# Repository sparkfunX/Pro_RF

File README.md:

SparkFun ProRF with RFM69/RFM95 LoRa
========================================

[*SparkX ProRF (SPX-14785)*](https://www.sparkfun.com/products/14785)

The Pro RF is the mind meld of a Pro Micro and a long-range RFM95W LoRa®-enabled radio. What you get is a very compact, easy to use Arduino with excellent point to point data transmission in the 915MHz ISM band. The Pro RF comes with a LiPo connector, a on-board LiPo charger, and a slide switch for On/Off. The board programs over a reinforced microB connector with a sleek reset button that fits nicely on the side of the board. We've even added our popular [Qwiic connector](https://www.sparkfun.com/qwiic) to the edge of the board making it incredibly fast to add sensors and actuators.

Thanks to the [Arduino LoRa library](https://github.com/sandeepmistry/arduino-LoRa), the RFM95W radio is an easy to use packet radio. But it doesn't stop at point-to-point packet radio because closing a few jumpers will give the Pro RF access to the DIO pins on the RFM95W which are necessary to operate in LoRaWAN mode, so you can use the Pro RF as a LoRaWAN node in a distributed sensor network such as [The Things Network](https://www.thethingsnetwork.org/).

The Pro RF also includes a power switch and 2-pin JST connector for powering from a lithium battery. With the power switch in the off position, the Pro RF will even charge the attached battery! 

And stop running out of ground pins! Every pin on the Pro RF is accompanied with a ground connection making buttons and LEDs super easy to connect. And in case your building something to be embedded into clothing or other physically harsh environment the antenna includes a stress relief hole to make sure your wire antenna survives.

Although a short (3 inch) wire antenna is sufficient for short distances (up to 1 mile line-of-sight), LoRa® is theoretically capable of covering extremely long distances (several miles) using the proper antenna. We've included the sketches we used for [range testing](https://cdn.sparkfun.com/assets/7/d/b/4/f/ProRF_RFM95.zip).

Checkout the [Pro Micro hookup guide](https://learn.sparkfun.com/tutorials/pro-micro--fio-v3-hookup-guide) as a general starting point for the Pro RF.

SparkFun labored with love to create this code. Feel like supporting open source hardware? 
Buy a [breakout board](https://www.sparkfun.com/products/14785) from SparkFun!

Repository Contents
-------------------

* **/Examples** - Example sketches showing how to setup the radio for maximuim range
* **/Hardware** - Eagle design files (.brd, .sch)

License Information
-------------------

This product is _**open source**_! 

If you have any questions or concerns on licensing, please contact techsupport@sparkfun.com.

Please use, reuse, and modify these files as you see fit. Please maintain attribution to SparkFun Electronics and release any derivative under the same license.

Distributed as-is; no warranty is given.

- Your friends at SparkFun.

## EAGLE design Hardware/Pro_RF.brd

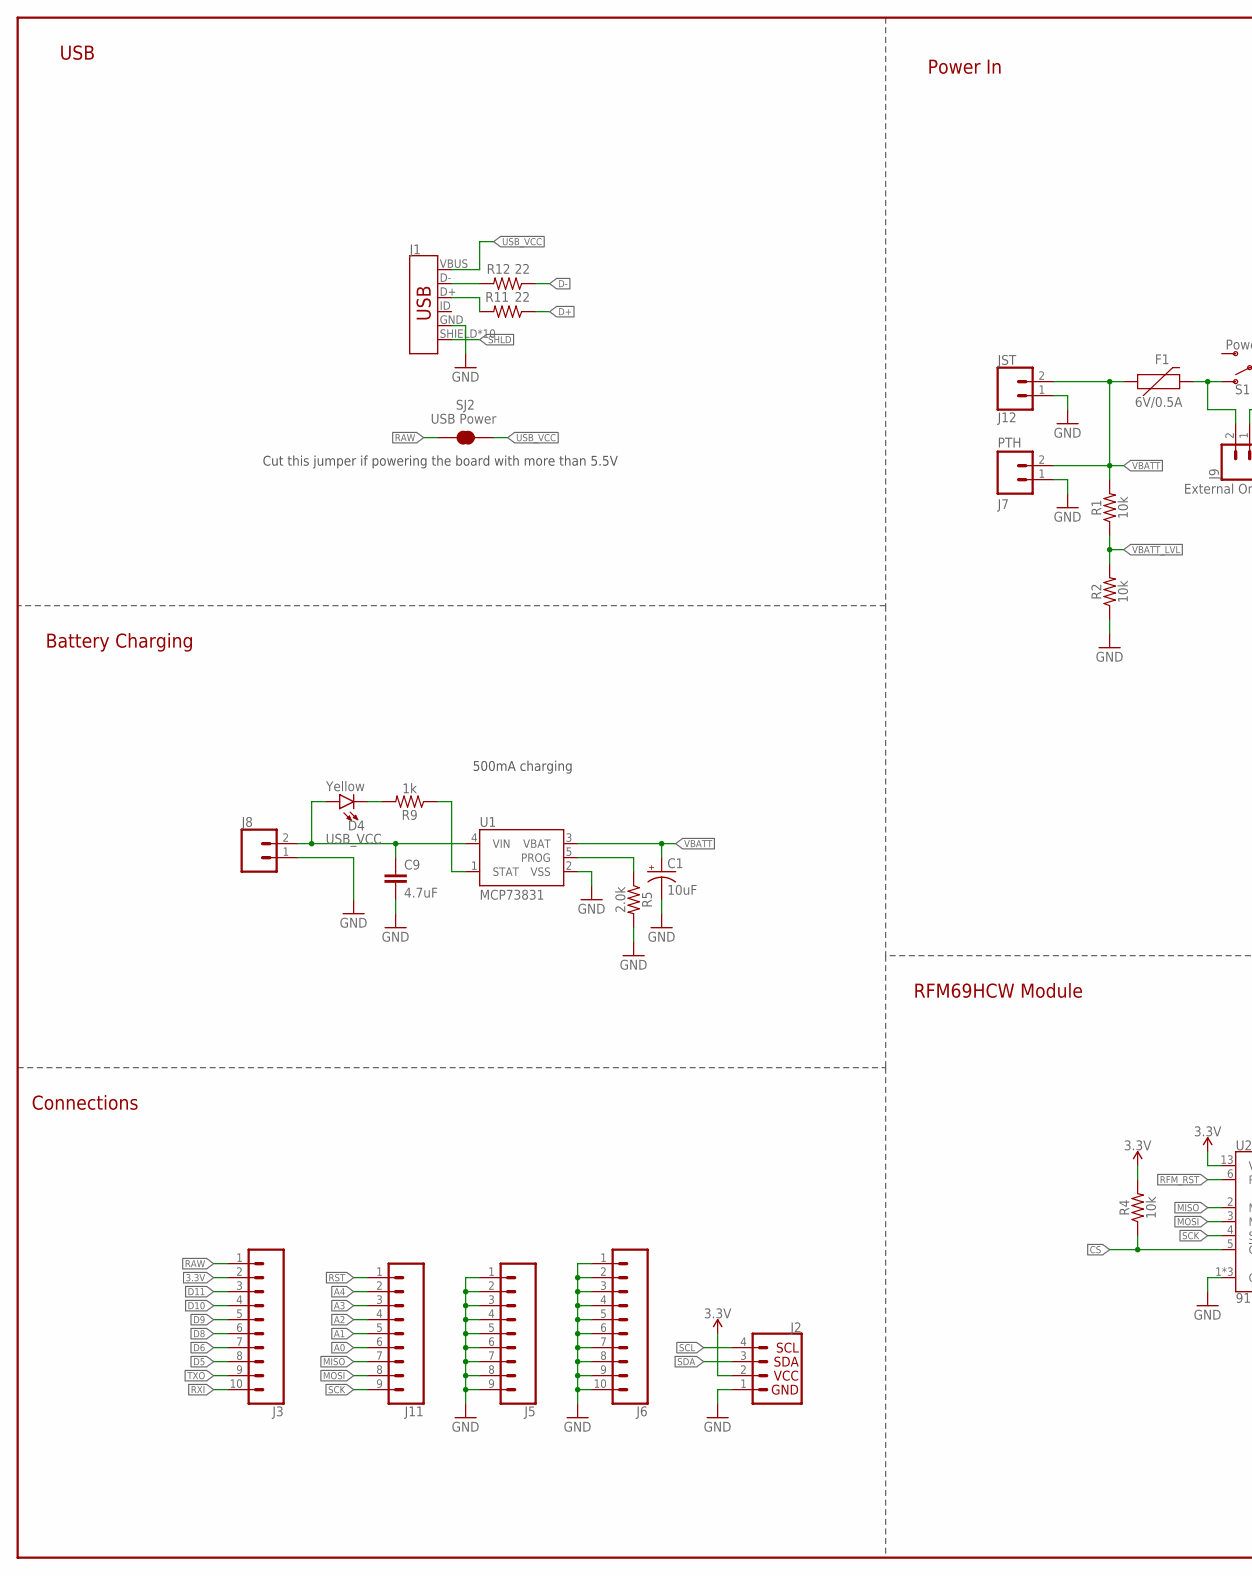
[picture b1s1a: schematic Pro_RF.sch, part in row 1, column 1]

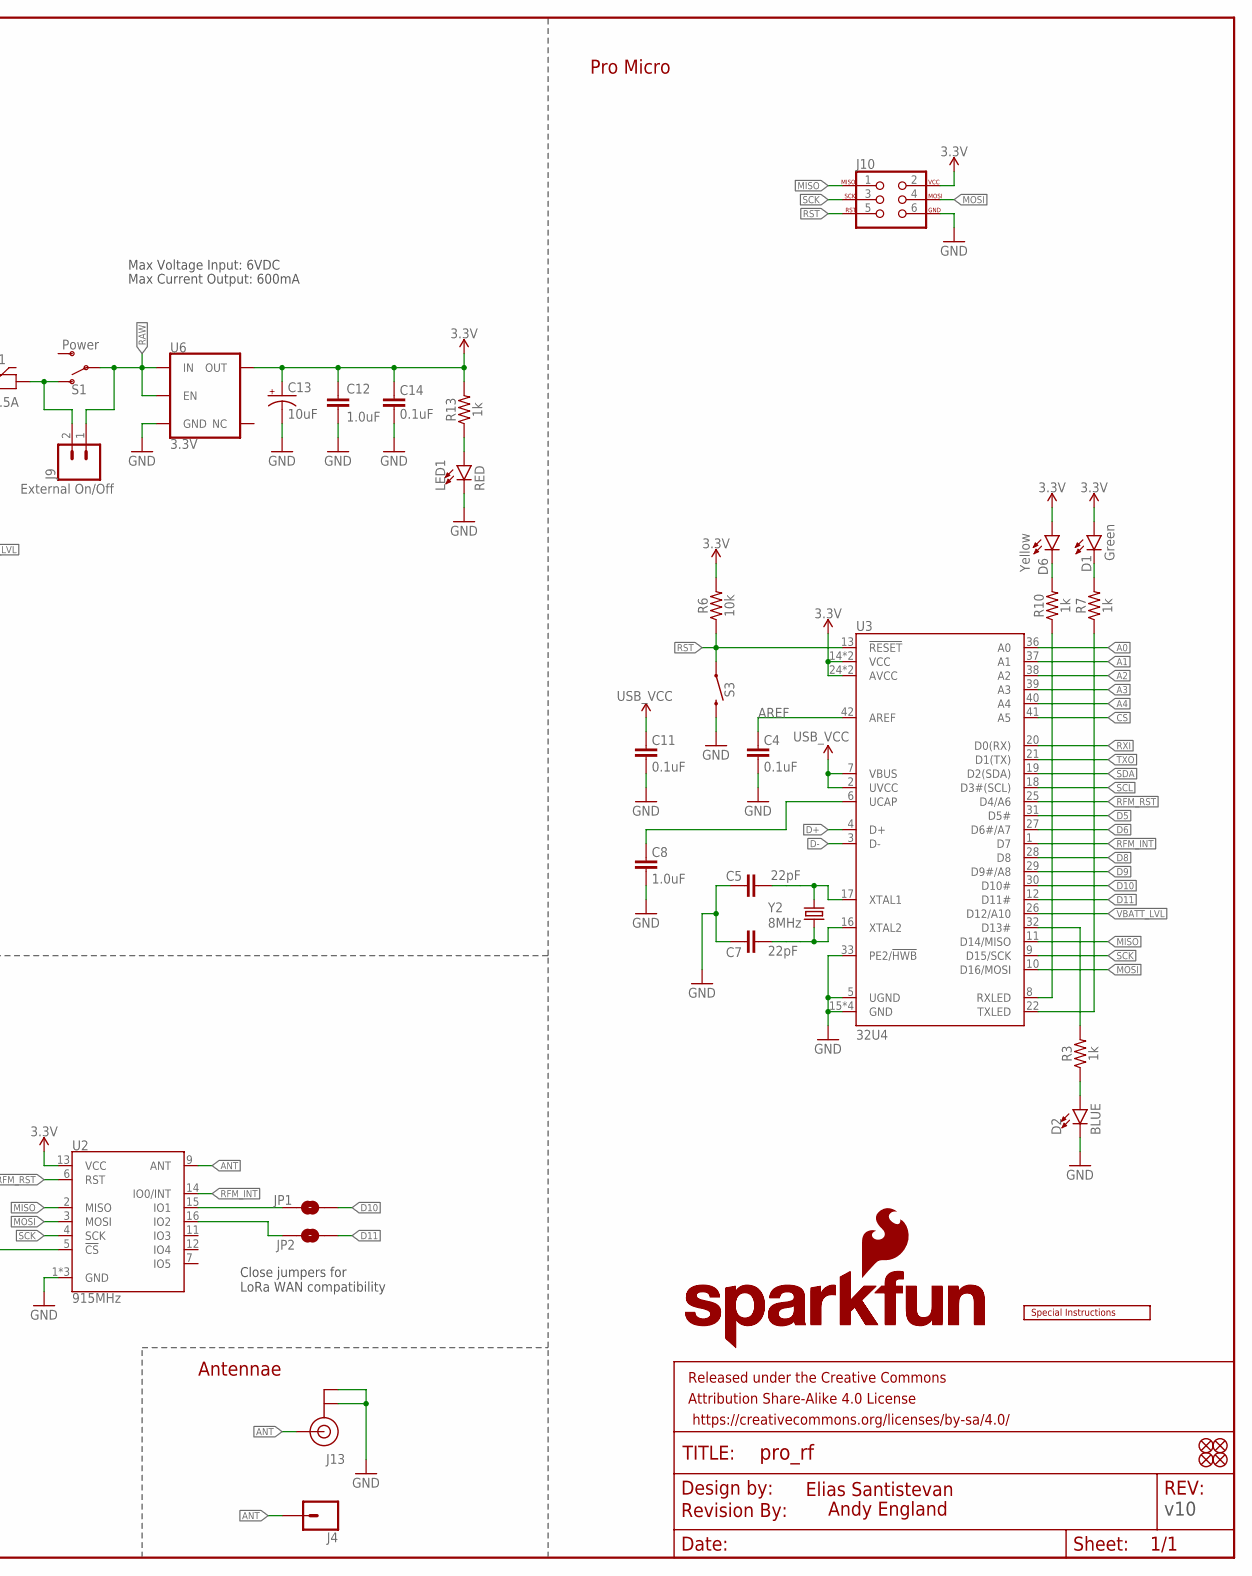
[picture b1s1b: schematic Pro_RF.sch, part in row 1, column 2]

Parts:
C1, C13: 10uF; EIA3216
C4, C11, C14: 0.1uF; 0603
C5, C7: 22pF; 0603
C8, C12: 1.0uF; 0603
C9: 4.7uF; 0603
D1: Green; LED-0603
D2: BLUE; LED-0603
D4, D6: Yellow; LED-0603
F1: 6V/0.5A; 1206
FD1, FD2, FD3, FD4: FIDUCIAL1X2; FIDUCIAL-1X2
FRAME2: FRAME-LEDGER; CREATIVE_COMMONS
J1: USB_MICRO-B_HALF_PTH_MILL; USB-MICROB-PTH-MILL
J2: QWIIC_CONNECTORJS-1MM; 1X04_1MM_RA
J3, J6: CONN_10NO_SILK_PTH_FEMALE; 1X10_NO_SILK
J4: CONN_01PTH_NO_SILK_YES_STOP; 1X01_NO_SILK
J5, J11: CONN_09NO_SILK; 1X09_NO_SILK
J7: PTH; 1X02_NO_SILK
J8: CONN_021X02_NO_SILK; 1X02_NO_SILK
J9: External On/Off; 1X02_NO_SILK
J10: AVR_SPI_PROG_3X2TESTPOINTS; 2X3_TEST_POINTS
J12: JST; JST-2-SMD
J13: U.FL
JP1, JP2: JUMPER-SMT_2_NO_SILK; SMT-JUMPER_2_NO_SILK
LED1: RED; LED-0603
LOGO1: REVISION
LOGO2: SFE_LOGO_NAME.1_INCH; SFE_LOGO_NAME_.1
LOGO3: SFE_LOGO_NAME_FLAME.1_INCH; SFE_LOGO_NAME_FLAME_.1
R1, R2, R4, R6: 10k; 0603
R3, R7, R9, R10, R13: 1k; 0603
R5: 2.0k; 0603
R11, R12: 22; 0603
S1: Power; SWITCH_SPST_SMD_A
S3: MOMENTARY-SWITCH-SPST-SMD-RIGHT-ANGLE; TACTILE_SWITCH_SMD_RIGHT_ANGLE
SJ2: USB Power; SMT-JUMPER_2_NC_TRACE_SILK
U1: MCP73831; SOT23-5
U2: 915MHz; RFM69HCW-XXXS2
U3: 32U4; QFN-44-NOPAD
U6: 3.3V; SOT23-5
U$26: SPECIAL_INSTRUCTIONS-ORDERING; ORDERING_INSTRUCTIONS
Y2: 8MHz; CRYSTAL-SMD-5X3.2-4PAD

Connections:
3.3V: C12.1, C13.+, C14.2, D1.A, D6.A, J2.2, J3.2, J10.2, R4.2, R6.2, R13.2, U2.13 (VCC), U3.14 (VCC), U3.24 (AVCC), U3.34 (VCC), U3.44 (AVCC), U6.5 (OUT)
!CS: R4.1, U2.5 (!CS), U3.41 (A5)
!RST: J10.5, J11.1, R6.1, S3.1, U3.13 (!RESET)
A0: J11.6, U3.36 (A0)
A1: J11.5, U3.37 (A1)
A2: J11.4, U3.38 (A2)
A3: J11.3, U3.39 (A3)
A4: J11.2, U3.40 (A4)
ANT: J4.1, J13.FEED (SIGNAL), U2.9 (ANT)
AREF: C4.2, U3.42 (AREF)
CHARGE_STAT: R9.1, U1.1 (STAT)
D5: J3.8, U3.31 (D5#)
D6: J3.7, U3.27 (D6#/A7)
D8: J3.6, U3.28 (D8)
D9: J3.5, U3.29 (D9#/A8)
D10: J3.4, JP1.2, U3.30 (D10#)
D11: J3.3, JP2.2, U3.12 (D11#)
D+: R11.1, U3.4 (D+)
D-: R12.1, U3.3 (D-)
GND: C1.-, C4.1, C5.2, C7.2, C8.1, C9.2, C11.1, C12.2, C13.-, C14.1, D2.C, J1.GND, J2.1, J5.1, J5.2, J5.3, J5.4, J5.5, J5.6, J5.7, J5.8, J5.9, J6.1, J6.2, J6.3, J6.4, J6.5, J6.6, J6.7, J6.8, J6.9, J6.10, J7.1, J8.1, J10.6, J12.1 (2), J13.1 (GND), J13.2 (GND), LED1.C, R2.1, R5.2, S3.2, U1.2 (VSS), U2.1 (GND), U2.8 (GND), U2.10 (GND), U3.5 (UGND), U3.15 (GND), U3.23 (GND), U3.33 (PE2/!HWB), U3.35 (GND), U3.43 (GND), U6.2 (GND)
MISO: J10.1, J11.7, U2.2 (MISO), U3.11 (D14/MISO)
MOSI: J10.4, J11.8, U2.3 (MOSI), U3.10 (D16/MOSI)
unnamed: D6.C, R10.2
unnamed: D1.C, R7.2
unnamed: D2.A, R3.1
unnamed: C5.1, U3.17 (XTAL1), Y2.3 (2)
unnamed: J1.D+, R11.2
unnamed: C7.1, U3.16 (XTAL2), Y2.1
unnamed: D4.C, R9.2
unnamed: F1.2, J9.2, S1.1 (O)
unnamed: R5.1, U1.5 (PROG)
unnamed: J1.D-, R12.2
unnamed: LED1.A, R13.1
RAW: J3.1, J9.1, S1.2, SJ2.1, U6.1 (IN), U6.3 (EN)
RFM_INT: U2.14 (IO0/INT), U3.1 (D7)
RFM_IO1: JP1.1, U2.15 (IO1)
RFM_IO2: JP2.1, U2.16 (IO2)
RFM_RST: U2.6 (RST), U3.25 (D4/A6)
RXI: J3.10, U3.20 (D0(RX))
RXLED: R10.1, U3.8 (RXLED)
SCK: J10.3, J11.9, U2.4 (SCK), U3.9 (D15/SCK)
SCL: J2.4, U3.18 (D3#(SCL))
SDA: J2.3, U3.19 (D2(SDA))
SHLD: J1.SHIELD, J1.SHIELD2 (SHIELD), J1.SHIELD3 (SHIELD), J1.SHIELD4 (SHIELD), J1.SHIELD5 (SHIELD), J1.SHIELD6 (SHIELD), J1.SHIELD7 (SHIELD), J1.SHIELD8 (SHIELD), J1.SHIELD9 (SHIELD), J1.SHIELD10 (SHIELD)
STAT: R3.2, U3.32 (D13#)
TXLED: R7.1, U3.22 (TXLED)
TXO: J3.9, U3.21 (D1(TX))
UCAP: C8.2, U3.6 (UCAP)
USB_VCC: C9.1, C11.2, D4.A, J1.VBUS, J8.2, SJ2.2, U1.4 (VIN), U3.2 (UVCC), U3.7 (VBUS)
VBATT: C1.+, F1.1, J7.2, J12.2 (1), R1.2, U1.3 (VBAT)
VBATT_LVL: R1.1, R2.2, U3.26 (D12/A10)

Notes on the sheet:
Max Voltage Input: 6VDC
Max Current Output: 600mA
Cut this jumper if powering the board with more than 5.5V
500mA charging
Close jumpers for LoRa WAN compatibility
Battery Charging
Power In
Pro Micro
RFM69HCW Module
v10
Andy England
Connections
Elias Santistevan
USB
Antennae

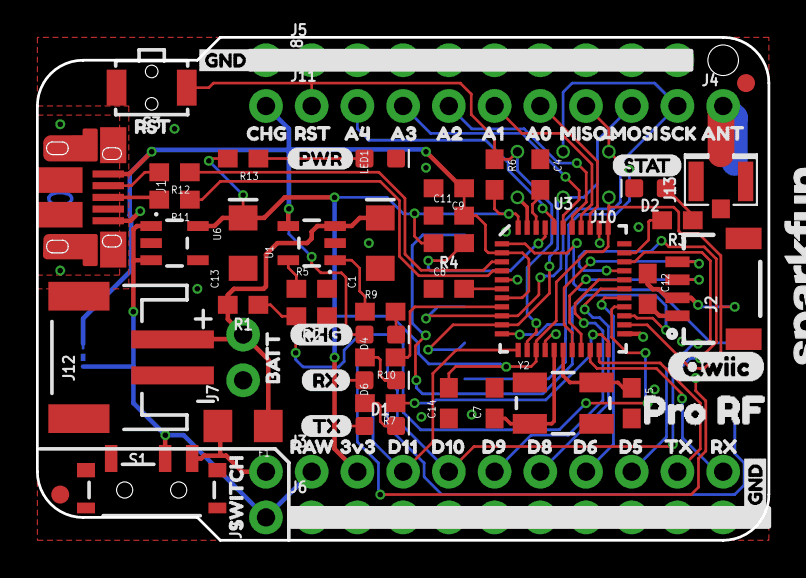
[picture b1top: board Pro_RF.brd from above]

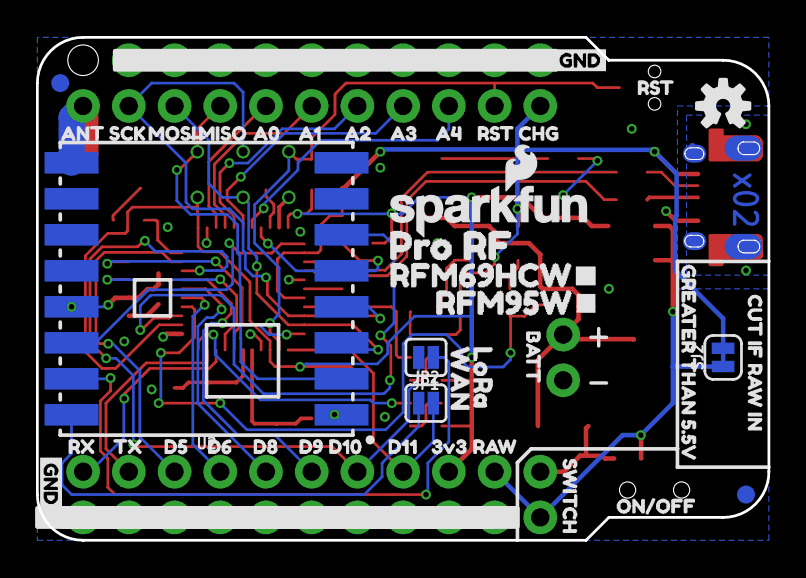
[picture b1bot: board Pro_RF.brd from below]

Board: 2 copper layers, 40.6 x 27.9 mm, 128 parts (42 on the bottom side), 51 nets.

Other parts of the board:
U$1, U$31: PRO_RF0
U$3, U$42: A43
U$4, U$43: A34
U$5, U$44: A25
U$6, U$45: A16
U$7, U$46: A07
U$8, U$47: MISO8
U$9, U$48: MOSI9
U$10, U$49: SCK10
U$11, U$50: ANT11
U$12, U$17, U$38, U$62: GND0
U$13, U$28, U$36, U$41: RST2
U$14, U$40, U$65: CHG1
U$15, U$16: D90
U$18, U$58: D615
U$19, U$73: RX2
U$20, U$56: D817
U$21, U$68: D100
U$22, U$54: D1119
U$23, U$53: 3V320
U$24, U$52: RAW21
U$25: LORA0
U$27, U$37: SWITCH23
U$29, U$32: BATT25
U$33: CUT_IF_RAW_IN0
U$34: GREATER_THAN_5#5V1
U$35: WAN1
U$39: ON#OFF0
U$51: OSHW-LOGO-S
U$55, U$74: D514
U$57, U$69: TX3
U$59: RFM69HCW#1
U$60: RFM95W#0
U$63: PWR-()-03
U$66: QWIIC-()-04
U$70: TX6
U$71: STAT5
U$72: RX7

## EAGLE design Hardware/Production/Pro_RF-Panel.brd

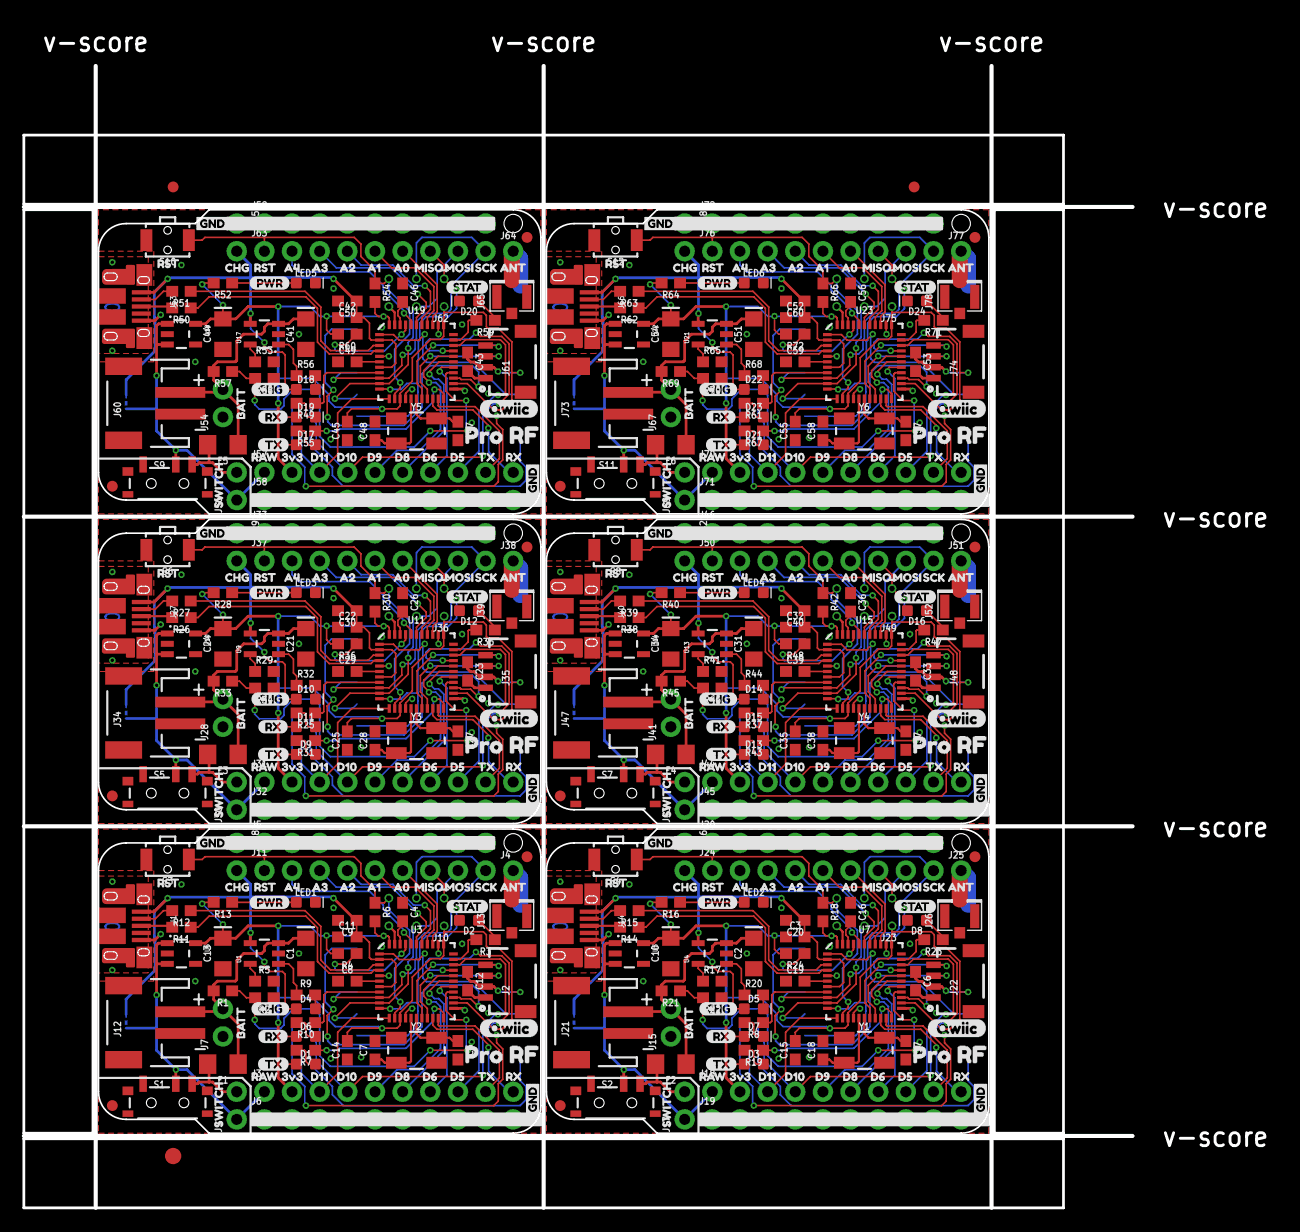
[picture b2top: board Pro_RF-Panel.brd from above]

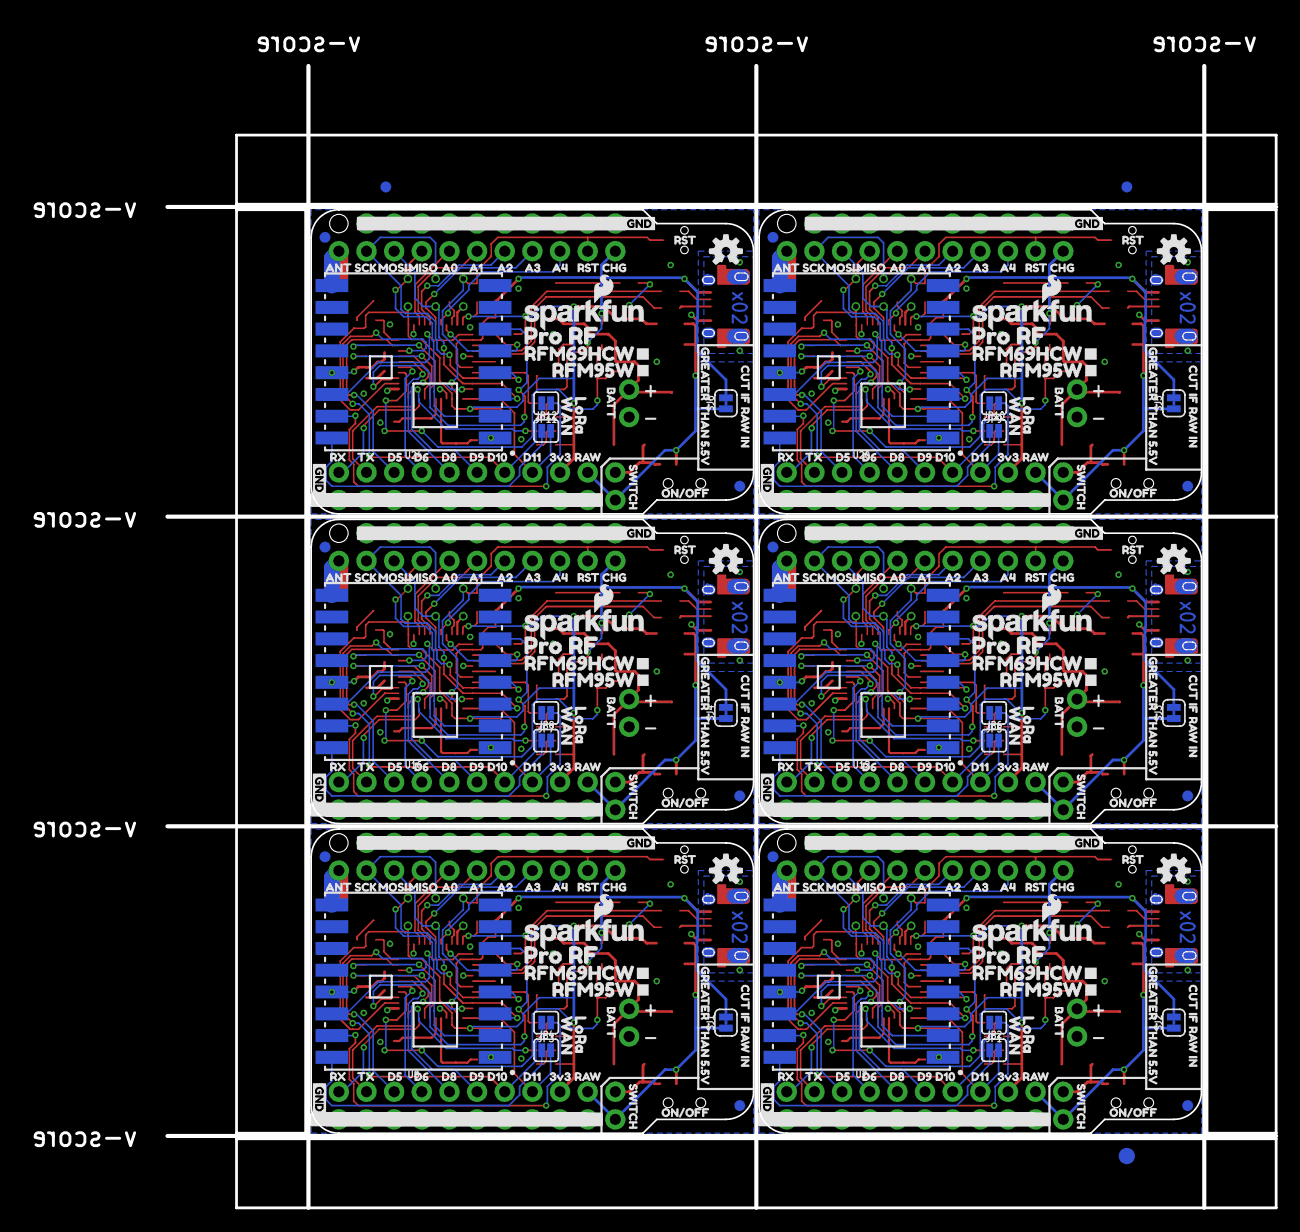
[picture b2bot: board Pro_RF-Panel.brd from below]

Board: 2 copper layers, 101.9 x 104.9 mm, 750 parts (255 on the bottom side), 306 nets.

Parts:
C1, C2, C10, C13, C21, C24, C31, C34, C41, C44, C51, C54: 10uF; EIA3216
C3, C4, C11, C14, C15, C16, C22, C25, C26, C32, C35, C36, C42, C45, C46, C52, C55, C56: 0.1uF; 0603
C5, C7, C17, C18, C27, C28, C37, C38, C47, C48, C57, C58: 22pF; 0603
C6, C8, C12, C19, C23, C29, C33, C39, C43, C49, C53, C59: 1.0uF; 0603
C9, C20, C30, C40, C50, C60: 4.7uF; 0603
D1, D3, D9, D13, D17, D21: Green; LED-0603
D2, D8, D12, D16, D20, D24: BLUE; LED-0603
D4, D5, D6, D7, D10, D11, D14, D15, D18, D19, D22, D23: Yellow; LED-0603
E$1, E$2, E$3, E$4: FIDUCIAL-1X2
E$5, E$6: FIDUCIAL-1.5X3
F1, F2, F3, F4, F5, F6: 6V/0.5A; 1206
FD1, FD2, FD3, FD4, FD5, FD6, FD7, FD8, FD9, FD10, FD11, FD12, FD13, FD14, FD15, FD16, FD17, FD18, FD19, FD20, FD21, FD22, FD23, FD24: FIDUCIAL1X2; FIDUCIAL-1X2
J1, J14, J27, J40, J53, J66: USB-MICROB-PTH-MILL
J2, J22, J35, J48, J61, J74: 1X04_1MM_RA
J3, J6, J18, J19, J31, J32, J44, J45, J57, J58, J70, J71: 1X10_NO_SILK
J4, J25, J38, J51, J64, J77: 1X01_NO_SILK
J5, J11, J20, J24, J33, J37, J46, J50, J59, J63, J72, J76: 1X09_NO_SILK
J7, J15, J28, J41, J54, J67: PTH; 1X02_NO_SILK
J8, J16, J29, J42, J55, J68: 1X02_NO_SILK
J9, J17, J30, J43, J56, J69: External On/Off; 1X02_NO_SILK
J10, J23, J36, J49, J62, J75: AVR_SPI_PROG_3X2TESTPOINTS; 2X3_TEST_POINTS
J12, J21, J34, J47, J60, J73: JST; JST-2-SMD
J13, J26, J39, J52, J65, J78: U.FL
JP1, JP2, JP3, JP4, JP5, JP6, JP7, JP8, JP9, JP10, JP11, JP12: SMT-JUMPER_2_NO_SILK
LED1, LED2, LED3, LED4, LED5, LED6: RED; LED-0603
LOGO1, LOGO2, LOGO3, LOGO4, LOGO5, LOGO6: SFE_LOGO_NAME_FLAME.1_INCH; SFE_LOGO_NAME_FLAME_.1
R1, R2, R4, R6, R18, R21, R22, R24, R30, R33, R34, R36, R42, R45, R46, R48, R54, R57, R58, R60, R66, R69, R70, R72: 10k; 0603
R3, R7, R8, R9, R10, R13, R16, R19, R20, R23, R25, R28, R31, R32, R35, R37, R40, R43, R44, R47, R49, R52, R55, R56, R59, R61, R64, R67, R68, R71: 1k; 0603
R5, R17, R29, R41, R53, R65: 2.0k; 0603
R11, R12, R14, R15, R26, R27, R38, R39, R50, R51, R62, R63: 22; 0603
S1, S2, S5, S7, S9, S11: Power; SWITCH_SPST_SMD_A
S3, S4, S6, S8, S10, S12: TACTILE_SWITCH_SMD_RIGHT_ANGLE
SJ1, SJ2, SJ3, SJ4, SJ5, SJ6: USB Power; SMT-JUMPER_2_NC_TRACE_SILK
U1, U4, U9, U13, U17, U21: MCP73831; SOT23-5
U2, U8, U12, U16, U20, U24: 915MHz; RFM69HCW-XXXS2
U3, U7, U11, U15, U19, U23: 32U4; QFN-44-NOPAD
U5, U6, U10, U14, U18, U22: 3.3V; SOT23-5
U$1, U$2, U$31, U$90, U$137, U$158, U$205, U$226, U$273, U$294, U$341, U$362: PRO_RF0
U$3, U$26, U$42, U$100, U$138, U$168, U$206, U$236, U$274, U$304, U$342, U$372: A43
U$4, U$30, U$43, U$101, U$139, U$169, U$207, U$237, U$275, U$305, U$343, U$373: A34
U$5, U$44, U$61, U$102, U$140, U$170, U$208, U$238, U$276, U$306, U$344, U$374: A25
U$6, U$45, U$64, U$103, U$141, U$171, U$209, U$239, U$277, U$307, U$345, U$375: A16
U$7, U$46, U$67, U$104, U$142, U$172, U$210, U$240, U$278, U$308, U$346, U$376: A07
U$8, U$47, U$75, U$105, U$143, U$173, U$211, U$241, U$279, U$309, U$347, U$377: MISO8
U$9, U$48, U$76, U$106, U$144, U$174, U$212, U$242, U$280, U$310, U$348, U$378: MOSI9
U$10, U$49, U$77, U$107, U$145, U$175, U$213, U$243, U$281, U$311, U$349, U$379: SCK10
U$11, U$50, U$78, U$108, U$146, U$176, U$214, U$244, U$282, U$312, U$350, U$380: ANT11
U$12, U$17, U$38, U$62, U$79, U$96, U$115, U$130, U$147, U$164, U$183, U$198, U$215, U$232, U$251, U$266, U$283, U$300, U$319, U$334, U$351, U$368, U$387, U$402: GND0
U$13, U$28, U$36, U$41, U$80, U$88, U$94, U$99, U$148, U$156, U$162, U$167, U$216, U$224, U$230, U$235, U$284, U$292, U$298, U$303, U$352, U$360, U$366, U$371: RST2
U$14, U$40, U$65, U$81, U$98, U$123, U$149, U$166, U$191, U$217, U$234, U$259, U$285, U$302, U$327, U$353, U$370, U$395: CHG1
U$15, U$16, U$128, U$129, U$196, U$197, U$264, U$265, U$332, U$333, U$400, U$401: D90
U$18, U$58, U$82, U$114, U$150, U$182, U$218, U$250, U$286, U$318, U$354, U$386: D615
U$19, U$73, U$122, U$131, U$190, U$199, U$258, U$267, U$326, U$335, U$394, U$403: RX2
U$20, U$56, U$83, U$113, U$151, U$181, U$219, U$249, U$287, U$317, U$355, U$385: D817
U$21, U$68, U$124, U$125, U$192, U$193, U$260, U$261, U$328, U$329, U$396, U$397: D100
U$22, U$54, U$84, U$112, U$152, U$180, U$220, U$248, U$288, U$316, U$356, U$384: D1119
U$23, U$53, U$85, U$111, U$153, U$179, U$221, U$247, U$289, U$315, U$357, U$383: 3V320
U$24, U$52, U$86, U$110, U$154, U$178, U$222, U$246, U$290, U$314, U$358, U$382: RAW21
U$25, U$135, U$203, U$271, U$339, U$407: LORA0
U$27, U$37, U$87, U$95, U$155, U$163, U$223, U$231, U$291, U$299, U$359, U$367: SWITCH23
U$29, U$32, U$89, U$91, U$157, U$159, U$225, U$227, U$293, U$295, U$361, U$363: BATT25
U$33, U$92, U$160, U$228, U$296, U$364: CUT_IF_RAW_IN0
U$34, U$93, U$161, U$229, U$297, U$365: GREATER_THAN_5#5V1
U$35, U$136, U$204, U$272, U$340, U$408: WAN1
U$39, U$97, U$165, U$233, U$301, U$369: ON#OFF0
U$51, U$109, U$177, U$245, U$313, U$381: OSHW-LOGO-S
U$55, U$74, U$126, U$127, U$194, U$195, U$262, U$263, U$330, U$331, U$398, U$399: D514
U$57, U$69, U$118, U$132, U$186, U$200, U$254, U$268, U$322, U$336, U$390, U$404: TX3
U$59, U$133, U$201, U$269, U$337, U$405: RFM69HCW#1
U$60, U$134, U$202, U$270, U$338, U$406: RFM95W#0
U$63, U$116, U$184, U$252, U$320, U$388: PWR-()-03
U$66, U$117, U$185, U$253, U$321, U$389: QWIIC-()-04
U$70, U$119, U$187, U$255, U$323, U$391: TX6
U$71, U$120, U$188, U$256, U$324, U$392: STAT5
U$72, U$121, U$189, U$257, U$325, U$393: RX7
Y1, Y2, Y3, Y4, Y5, Y6: 8MHz; CRYSTAL-SMD-5X3.2-4PAD

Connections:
3.3V: C12.1, C13.+, C14.2, D1.A, D6.A, J2.2, J3.2, J10.2, R4.2, R6.2, R13.2, U2.13, U3.14, U3.24, U3.34, U3.44, U6.5
3.3V1: C6.1, C10.+, C15.2, D3.A, D7.A, J18.2, J22.2, J23.2, R16.2, R18.2, R24.2, U5.5, U7.14, U7.24, U7.34, U7.44, U8.13
3.3V2: C23.1, C24.+, C25.2, D9.A, D11.A, J31.2, J35.2, J36.2, R28.2, R30.2, R36.2, U10.5, U11.14, U11.24, U11.34, U11.44, U12.13
3.3V3: C33.1, C34.+, C35.2, D13.A, D15.A, J44.2, J48.2, J49.2, R40.2, R42.2, R48.2, U14.5, U15.14, U15.24, U15.34, U15.44, U16.13
3.3V4: C43.1, C44.+, C45.2, D17.A, D19.A, J57.2, J61.2, J62.2, R52.2, R54.2, R60.2, U18.5, U19.14, U19.24, U19.34, U19.44, U20.13
3.3V5: C53.1, C54.+, C55.2, D21.A, D23.A, J70.2, J74.2, J75.2, R64.2, R66.2, R72.2, U22.5, U23.14, U23.24, U23.34, U23.44, U24.13
!CS: R4.1, U2.5, U3.41
!CS1: R24.1, U7.41, U8.5
!CS2: R36.1, U11.41, U12.5
!CS3: R48.1, U15.41, U16.5
!CS4: R60.1, U19.41, U20.5
!CS5: R72.1, U23.41, U24.5
!RST: J10.5, J11.1, R6.1, S3.1, U3.13
!RST1: J23.5, J24.1, R18.1, S4.1, U7.13
!RST2: J36.5, J37.1, R30.1, S6.1, U11.13
!RST3: J49.5, J50.1, R42.1, S8.1, U15.13
!RST4: J62.5, J63.1, R54.1, S10.1, U19.13
!RST5: J75.5, J76.1, R66.1, S12.1, U23.13
A0: J11.6, U3.36
A1: J11.5, U3.37
A2: J11.4, U3.38
A3: J11.3, U3.39
A4: J11.2, U3.40
A5: J24.6, U7.36
A6: J24.5, U7.37
A7: J24.4, U7.38
A8: J24.3, U7.39
A9: J24.2, U7.40
A10: J37.6, U11.36
A11: J37.5, U11.37
A12: J37.4, U11.38
A13: J37.3, U11.39
A14: J37.2, U11.40
A15: J50.6, U15.36
A16: J50.5, U15.37
A17: J50.4, U15.38
A18: J50.3, U15.39
A19: J50.2, U15.40
A20: J63.6, U19.36
A21: J63.5, U19.37
A22: J63.4, U19.38
A23: J63.3, U19.39
A24: J63.2, U19.40
A25: J76.6, U23.36
A26: J76.5, U23.37
A27: J76.4, U23.38
A28: J76.3, U23.39
A29: J76.2, U23.40
ANT: J4.1, J13.FEED, U2.9
ANT1: J25.1, J26.FEED, U8.9
ANT2: J38.1, J39.FEED, U12.9
ANT3: J51.1, J52.FEED, U16.9
ANT4: J64.1, J65.FEED, U20.9
ANT5: J77.1, J78.FEED, U24.9
AREF: C4.2, U3.42
AREF1: C16.2, U7.42
AREF2: C26.2, U11.42
AREF3: C36.2, U15.42
AREF4: C46.2, U19.42
AREF5: C56.2, U23.42
CHARGE_STAT: R9.1, U1.1
CHARGE_STAT1: R20.1, U4.1
CHARGE_STAT2: R32.1, U9.1
CHARGE_STAT3: R44.1, U13.1
CHARGE_STAT4: R56.1, U17.1
CHARGE_STAT5: R68.1, U21.1
D1: J18.8, U7.31
D2: J18.7, U7.27
D3: J18.6, U7.28
D4: J18.4, JP3.2, U7.30
D5: J3.8, U3.31
D6: J3.7, U3.27
D7: J18.5, U7.29
D8: J3.6, U3.28
D9: J3.5, U3.29
D10: J3.4, JP1.2, U3.30
D11: J3.3, JP2.2, U3.12
D12: J18.3, JP4.2, U7.12
D13: J31.8, U11.31
D14: J31.7, U11.27
D15: J31.6, U11.28
D16: J31.4, JP5.2, U11.30
D17: J31.5, U11.29
D18: J31.3, JP6.2, U11.12
D19: J44.8, U15.31
D20: J44.7, U15.27
D21: J44.6, U15.28
D22: J44.4, JP7.2, U15.30
D23: J44.5, U15.29
D24: J44.3, JP8.2, U15.12
D25: J57.8, U19.31
D26: J57.7, U19.27
D27: J57.6, U19.28
D28: J57.4, JP9.2, U19.30
D29: J57.5, U19.29
D30: J57.3, JP10.2, U19.12
D31: J70.8, U23.31
D32: J70.7, U23.27
D33: J70.6, U23.28
D34: J70.4, JP11.2, U23.30
D35: J70.5, U23.29
D36: J70.3, JP12.2, U23.12
D+: R11.1, U3.4
D+1: R14.1, U7.4
D+2: R26.1, U11.4
D+3: R38.1, U15.4
D+4: R50.1, U19.4
D+5: R62.1, U23.4
D-: R12.1, U3.3
D-1: R15.1, U7.3
D-2: R27.1, U11.3
D-3: R39.1, U15.3
D-4: R51.1, U19.3
D-5: R63.1, U23.3
GND: C1.-, C4.1, C5.2, C7.2, C8.1, C9.2, C11.1, C12.2, C13.-, C14.1, D2.C, J1.GND, J2.1, J5.1, J5.2, J5.3, J5.4, J5.5, J5.6, J5.7, J5.8, J5.9, J6.1, J6.2, J6.3, J6.4, J6.5, J6.6, J6.7, J6.8, J6.9, J6.10, J7.1, J8.1, J10.6, J12.1, J13.1, J13.2, LED1.C, R2.1, R5.2, S3.2, U1.2, U2.1, U2.8, U2.10, U3.5, U3.15, U3.23, U3.33, U3.35, U3.43, U6.2
GND1: C2.-, C3.1, C6.2, C10.-, C15.1, C16.1, C17.2, C18.2, C19.1, C20.2, D8.C, J14.GND, J15.1, J16.1, J19.1, J19.2, J19.3, J19.4, J19.5, J19.6, J19.7, J19.8, J19.9, J19.10, J20.1, J20.2, J20.3, J20.4, J20.5, J20.6, J20.7, J20.8, J20.9, J21.1, J22.1, J23.6, J26.1, J26.2, LED2.C, R17.2, R22.1, S4.2, U4.2, U5.2, U7.5, U7.15, U7.23, U7.33, U7.35, U7.43, U8.1, U8.8, U8.10
GND2: C21.-, C22.1, C23.2, C24.-, C25.1, C26.1, C27.2, C28.2, C29.1, C30.2, D12.C, J27.GND, J28.1, J29.1, J32.1, J32.2, J32.3, J32.4, J32.5, J32.6, J32.7, J32.8, J32.9, J32.10, J33.1, J33.2, J33.3, J33.4, J33.5, J33.6, J33.7, J33.8, J33.9, J34.1, J35.1, J36.6, J39.1, J39.2, LED3.C, R29.2, R34.1, S6.2, U9.2, U10.2, U11.5, U11.15, U11.23, U11.33, U11.35, U11.43, U12.1, U12.8, U12.10
GND3: C31.-, C32.1, C33.2, C34.-, C35.1, C36.1, C37.2, C38.2, C39.1, C40.2, D16.C, J40.GND, J41.1, J42.1, J45.1, J45.2, J45.3, J45.4, J45.5, J45.6, J45.7, J45.8, J45.9, J45.10, J46.1, J46.2, J46.3, J46.4, J46.5, J46.6, J46.7, J46.8, J46.9, J47.1, J48.1, J49.6, J52.1, J52.2, LED4.C, R41.2, R46.1, S8.2, U13.2, U14.2, U15.5, U15.15, U15.23, U15.33, U15.35, U15.43, U16.1, U16.8, U16.10
GND4: C41.-, C42.1, C43.2, C44.-, C45.1, C46.1, C47.2, C48.2, C49.1, C50.2, D20.C, J53.GND, J54.1, J55.1, J58.1, J58.2, J58.3, J58.4, J58.5, J58.6, J58.7, J58.8, J58.9, J58.10, J59.1, J59.2, J59.3, J59.4, J59.5, J59.6, J59.7, J59.8, J59.9, J60.1, J61.1, J62.6, J65.1, J65.2, LED5.C, R53.2, R58.1, S10.2, U17.2, U18.2, U19.5, U19.15, U19.23, U19.33, U19.35, U19.43, U20.1, U20.8, U20.10
GND5: C51.-, C52.1, C53.2, C54.-, C55.1, C56.1, C57.2, C58.2, C59.1, C60.2, D24.C, J66.GND, J67.1, J68.1, J71.1, J71.2, J71.3, J71.4, J71.5, J71.6, J71.7, J71.8, J71.9, J71.10, J72.1, J72.2, J72.3, J72.4, J72.5, J72.6, J72.7, J72.8, J72.9, J73.1, J74.1, J75.6, J78.1, J78.2, LED6.C, R65.2, R70.1, S12.2, U21.2, U22.2, U23.5, U23.15, U23.23, U23.33, U23.35, U23.43, U24.1, U24.8, U24.10
MISO: J10.1, J11.7, U2.2, U3.11
MISO1: J23.1, J24.7, U7.11, U8.2
MISO2: J36.1, J37.7, U11.11, U12.2
MISO3: J49.1, J50.7, U15.11, U16.2
MISO4: J62.1, J63.7, U19.11, U20.2
MISO5: J75.1, J76.7, U23.11, U24.2
MOSI: J10.4, J11.8, U2.3, U3.10
MOSI1: J23.4, J24.8, U7.10, U8.3
MOSI2: J36.4, J37.8, U11.10, U12.3
MOSI3: J49.4, J50.8, U15.10, U16.3
MOSI4: J62.4, J63.8, U19.10, U20.3
MOSI5: J75.4, J76.8, U23.10, U24.3
unnamed: D6.C, R10.2
unnamed: D1.C, R7.2
unnamed: D2.A, R3.1
unnamed: C5.1, U3.17, Y2.3
unnamed: J1.D+, R11.2
unnamed: C7.1, U3.16, Y2.1
unnamed: J14.D-, R15.2
unnamed: D4.C, R9.2
unnamed: F1.2, J9.2, S1.1
unnamed: J14.D+, R14.2
unnamed: R5.1, U1.5
unnamed: F2.2, J17.2, S2.1
unnamed: R17.1, U4.5
unnamed: D5.C, R20.2
unnamed: LED2.A, R16.1
unnamed: D7.C, R8.2
unnamed: D3.C, R19.2
unnamed: D8.A, R23.1
unnamed: C17.1, U7.17, Y1.3
unnamed: J1.D-, R12.2
unnamed: C18.1, U7.16, Y1.1
unnamed: J27.D-, R27.2
unnamed: J27.D+, R26.2
unnamed: F3.2, J30.2, S5.1
unnamed: R29.1, U9.5
unnamed: D10.C, R32.2
unnamed: LED3.A, R28.1
unnamed: D11.C, R25.2
unnamed: D9.C, R31.2
unnamed: D12.A, R35.1
unnamed: C27.1, U11.17, Y3.3
unnamed: C28.1, U11.16, Y3.1
unnamed: J40.D-, R39.2
unnamed: J40.D+, R38.2
unnamed: F4.2, J43.2, S7.1
unnamed: R41.1, U13.5
unnamed: D14.C, R44.2
unnamed: LED1.A, R13.1
unnamed: LED4.A, R40.1
unnamed: D15.C, R37.2
unnamed: D13.C, R43.2
unnamed: D16.A, R47.1
unnamed: C37.1, U15.17, Y4.3
unnamed: C38.1, U15.16, Y4.1
unnamed: J53.D-, R51.2
unnamed: J53.D+, R50.2
unnamed: F5.2, J56.2, S9.1
unnamed: R53.1, U17.5
unnamed: D18.C, R56.2
unnamed: LED5.A, R52.1
unnamed: D19.C, R49.2
unnamed: D17.C, R55.2
unnamed: D20.A, R59.1
unnamed: C47.1, U19.17, Y5.3
unnamed: C48.1, U19.16, Y5.1
unnamed: J66.D-, R63.2
unnamed: J66.D+, R62.2
unnamed: F6.2, J69.2, S11.1
unnamed: R65.1, U21.5
unnamed: D22.C, R68.2
unnamed: LED6.A, R64.1
unnamed: D23.C, R61.2
unnamed: D21.C, R67.2
unnamed: D24.A, R71.1
unnamed: C57.1, U23.17, Y6.3
unnamed: C58.1, U23.16, Y6.1
RAW: J3.1, J9.1, S1.2, SJ2.1, U6.1, U6.3
RAW1: J17.1, J18.1, S2.2, SJ1.1, U5.1, U5.3
RAW2: J30.1, J31.1, S5.2, SJ3.1, U10.1, U10.3
RAW3: J43.1, J44.1, S7.2, SJ4.1, U14.1, U14.3
RAW4: J56.1, J57.1, S9.2, SJ5.1, U18.1, U18.3
RAW5: J69.1, J70.1, S11.2, SJ6.1, U22.1, U22.3
RFM_INT: U2.14, U3.1
RFM_INT1: U7.1, U8.14
RFM_INT2: U11.1, U12.14
RFM_INT3: U15.1, U16.14
RFM_INT4: U19.1, U20.14
RFM_INT5: U23.1, U24.14
RFM_IO1: JP1.1, U2.15
RFM_IO2: JP2.1, U2.16
RFM_IO3: JP3.1, U8.15
RFM_IO4: JP4.1, U8.16
RFM_IO5: JP5.1, U12.15
RFM_IO6: JP6.1, U12.16
RFM_IO7: JP7.1, U16.15
RFM_IO8: JP8.1, U16.16
RFM_IO9: JP9.1, U20.15
RFM_IO10: JP10.1, U20.16
RFM_IO11: JP11.1, U24.15
RFM_IO12: JP12.1, U24.16
RFM_RST: U2.6, U3.25
RFM_RST1: U7.25, U8.6
RFM_RST2: U11.25, U12.6
RFM_RST3: U15.25, U16.6
RFM_RST4: U19.25, U20.6
RFM_RST5: U23.25, U24.6
RXI: J3.10, U3.20
RXI1: J18.10, U7.20
RXI2: J31.10, U11.20
RXI3: J44.10, U15.20
RXI4: J57.10, U19.20
RXI5: J70.10, U23.20
RXLED: R10.1, U3.8
RXLED1: R8.1, U7.8
RXLED2: R25.1, U11.8
RXLED3: R37.1, U15.8
RXLED4: R49.1, U19.8
RXLED5: R61.1, U23.8
SCK: J10.3, J11.9, U2.4, U3.9
SCK1: J23.3, J24.9, U7.9, U8.4
SCK2: J36.3, J37.9, U11.9, U12.4
SCK3: J49.3, J50.9, U15.9, U16.4
SCK4: J62.3, J63.9, U19.9, U20.4
SCK5: J75.3, J76.9, U23.9, U24.4
SCL: J2.4, U3.18
SCL1: J22.4, U7.18
SCL2: J35.4, U11.18
SCL3: J48.4, U15.18
SCL4: J61.4, U19.18
SCL5: J74.4, U23.18
SDA: J2.3, U3.19
SDA1: J22.3, U7.19
SDA2: J35.3, U11.19
SDA3: J48.3, U15.19
SDA4: J61.3, U19.19
SDA5: J74.3, U23.19
SHLD: J1.SHIELD, J1.SHIELD2, J1.SHIELD3, J1.SHIELD4, J1.SHIELD5, J1.SHIELD6, J1.SHIELD7, J1.SHIELD8, J1.SHIELD9, J1.SHIELD10
SHLD1: J14.SHIELD, J14.SHIELD2, J14.SHIELD3, J14.SHIELD4, J14.SHIELD5, J14.SHIELD6, J14.SHIELD7, J14.SHIELD8, J14.SHIELD9, J14.SHIELD10
SHLD2: J27.SHIELD, J27.SHIELD2, J27.SHIELD3, J27.SHIELD4, J27.SHIELD5, J27.SHIELD6, J27.SHIELD7, J27.SHIELD8, J27.SHIELD9, J27.SHIELD10
SHLD3: J40.SHIELD, J40.SHIELD2, J40.SHIELD3, J40.SHIELD4, J40.SHIELD5, J40.SHIELD6, J40.SHIELD7, J40.SHIELD8, J40.SHIELD9, J40.SHIELD10
SHLD4: J53.SHIELD, J53.SHIELD2, J53.SHIELD3, J53.SHIELD4, J53.SHIELD5, J53.SHIELD6, J53.SHIELD7, J53.SHIELD8, J53.SHIELD9, J53.SHIELD10
SHLD5: J66.SHIELD, J66.SHIELD2, J66.SHIELD3, J66.SHIELD4, J66.SHIELD5, J66.SHIELD6, J66.SHIELD7, J66.SHIELD8, J66.SHIELD9, J66.SHIELD10
STAT: R3.2, U3.32
STAT1: R23.2, U7.32
STAT2: R35.2, U11.32
STAT3: R47.2, U15.32
STAT4: R59.2, U19.32
STAT5: R71.2, U23.32
TXLED: R7.1, U3.22
TXLED1: R19.1, U7.22
TXLED2: R31.1, U11.22
TXLED3: R43.1, U15.22
TXLED4: R55.1, U19.22
TXLED5: R67.1, U23.22
TXO: J3.9, U3.21
TXO1: J18.9, U7.21
TXO2: J31.9, U11.21
TXO3: J44.9, U15.21
TXO4: J57.9, U19.21
TXO5: J70.9, U23.21
UCAP: C8.2, U3.6
UCAP1: C19.2, U7.6
UCAP2: C29.2, U11.6
UCAP3: C39.2, U15.6
UCAP4: C49.2, U19.6
UCAP5: C59.2, U23.6
USB_VCC: C9.1, C11.2, D4.A, J1.VBUS, J8.2, SJ2.2, U1.4, U3.2, U3.7
USB_VCC1: C3.2, C20.1, D5.A, J14.VBUS, J16.2, SJ1.2, U4.4, U7.2, U7.7
USB_VCC2: C22.2, C30.1, D10.A, J27.VBUS, J29.2, SJ3.2, U9.4, U11.2, U11.7
USB_VCC3: C32.2, C40.1, D14.A, J40.VBUS, J42.2, SJ4.2, U13.4, U15.2, U15.7
USB_VCC4: C42.2, C50.1, D18.A, J53.VBUS, J55.2, SJ5.2, U17.4, U19.2, U19.7
USB_VCC5: C52.2, C60.1, D22.A, J66.VBUS, J68.2, SJ6.2, U21.4, U23.2, U23.7
VBATT: C1.+, F1.1, J7.2, J12.2, R1.2, U1.3
VBATT1: C2.+, F2.1, J15.2, J21.2, R21.2, U4.3
VBATT2: C21.+, F3.1, J28.2, J34.2, R33.2, U9.3
VBATT3: C31.+, F4.1, J41.2, J47.2, R45.2, U13.3
VBATT4: C41.+, F5.1, J54.2, J60.2, R57.2, U17.3
VBATT5: C51.+, F6.1, J67.2, J73.2, R69.2, U21.3
VBATT_LVL: R1.1, R2.2, U3.26
VBATT_LVL1: R21.1, R22.2, U7.26
VBATT_LVL2: R33.1, R34.2, U11.26
VBATT_LVL3: R45.1, R46.2, U15.26
VBATT_LVL4: R57.1, R58.2, U19.26
VBATT_LVL5: R69.1, R70.2, U23.26

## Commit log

2018-05-23 Many Prod_ID changes and a few FP changes.
2018-05-25 Adding prod IDs. This changed some FPs so fixed routes. Moved Int Pin to avoid I2C
2018-06-01 Many updates. v02.
2018-06-11 Adding pullup to CS
2018-06-26 Adding Examples
2018-06-26 Readme update
2018-06-26 gitignore update
2018-06-26 Removing backup files
2018-07-02 Adding Thing Network examples
2018-07-30 updating to sparkfun silk
2018-08-06 Clean up
2018-11-26 added production folder
    added a production folder for the boards that were just ordered

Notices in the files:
parts and their libraries:
SparkFun-Capacitors: Licensing: CC v3.0 Share-Alike You are welcome to use this library for commercial purposes.
SparkFun-LED: Licensing: Creative Commons ShareAlike 4.0 International - https://creativecommons.org/licenses/by-sa/4.0
SparkFun-Aesthetics: Released under the Creative Commons
